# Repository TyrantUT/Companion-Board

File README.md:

# Companion-Board
4 Channel DC Relay for HLT / Boil Contactors, and HLT / Boil PWM

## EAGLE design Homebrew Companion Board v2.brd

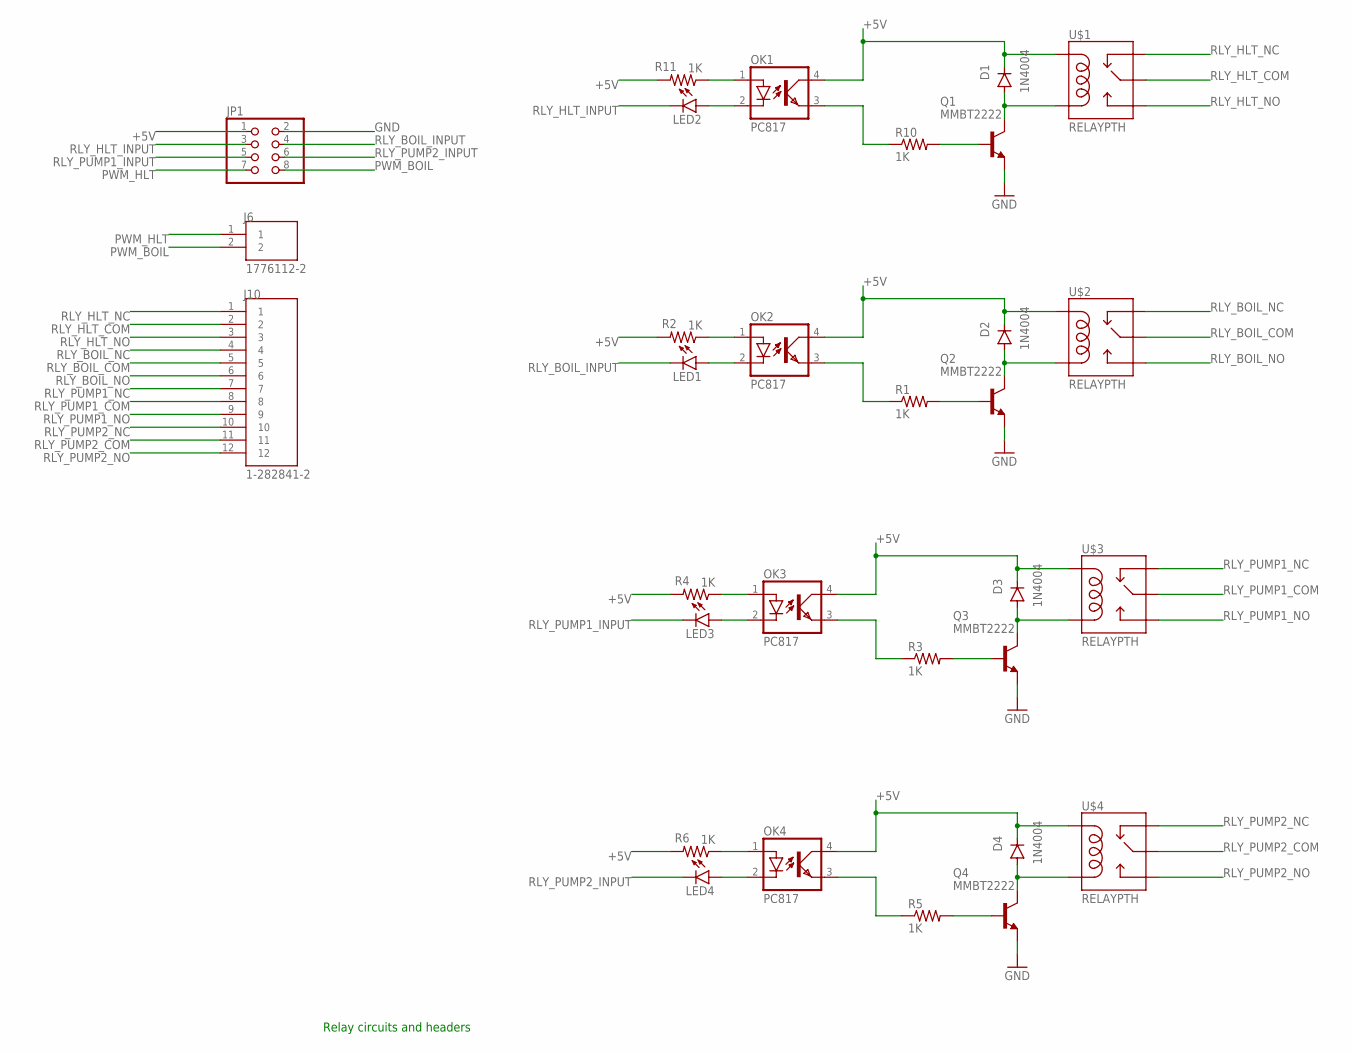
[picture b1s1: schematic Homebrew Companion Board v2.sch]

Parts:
D1, D2, D3, D4: 1N4004; DO41-10; MPN 1N4007-T
J6: 1776112-2; TE_1776112-2; MPN 1776112-2
J10: 1-282841-2; TE_1-282841-2; MPN 1-282841-2
JP1: PINHD-2X4; 2X04; MPN 826634-4
LED1, LED2, LED3, LED4: LEDCHIP-LED0805; CHIP-LED0805; MPN 5988110107F
OK1, OK2, OK3, OK4: PC817; DIL04; MPN HCPL-817-000E
Q1, Q2, Q3, Q4: MMBT2222; SOT23-BEC; MPN MMBT2222A-7-F
R1, R2, R3, R4, R5, R6, R10, R11: 1K; R0603; MPN AC0402FR-071KL
U$1, U$2, U$3, U$4: RELAYPTH; SRD-05VDC-SL-C

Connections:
+5V: D1.C, D2.C, D3.C, D4.C, JP1.1, OK1.4 (COL), OK2.4 (COL), OK3.4 (COL), OK4.4 (COL), R2.2, R4.2, R6.2, R11.2, U$1.COIL1, U$2.COIL1, U$3.COIL1, U$4.COIL1
GND: JP1.2, Q1.E, Q2.E, Q3.E, Q4.E
unnamed: D2.A, Q2.C, U$2.COIL0
unnamed: D1.A, Q1.C, U$1.COIL0
unnamed: LED2.A, OK1.2 (C)
unnamed: Q1.B, R10.2
unnamed: OK1.3 (EMIT), R10.1
unnamed: OK1.1 (A), R11.1
unnamed: LED1.A, OK2.2 (C)
unnamed: Q2.B, R1.2
unnamed: OK2.3 (EMIT), R1.1
unnamed: OK2.1 (A), R2.1
unnamed: D3.A, Q3.C, U$3.COIL0
unnamed: LED3.A, OK3.2 (C)
unnamed: Q3.B, R3.2
unnamed: OK3.3 (EMIT), R3.1
unnamed: OK3.1 (A), R4.1
unnamed: D4.A, Q4.C, U$4.COIL0
unnamed: LED4.A, OK4.2 (C)
unnamed: Q4.B, R5.2
unnamed: OK4.3 (EMIT), R5.1
unnamed: OK4.1 (A), R6.1
PWM_BOIL: J6.2, JP1.8
PWM_HLT: J6.1, JP1.7
RLY_BOIL_COM: J10.5, U$2.SWCOMMON
RLY_BOIL_INPUT: JP1.4, LED1.C
RLY_BOIL_NC: J10.4, U$2.SWCLOSED (SWCLOSE)
RLY_BOIL_NO: J10.6, U$2.SWOPEN
RLY_HLT_COM: J10.2, U$1.SWCOMMON
RLY_HLT_INPUT: JP1.3, LED2.C
RLY_HLT_NC: J10.1, U$1.SWCLOSED (SWCLOSE)
RLY_HLT_NO: J10.3, U$1.SWOPEN
RLY_PUMP1_COM: J10.8, U$3.SWCOMMON
RLY_PUMP1_INPUT: JP1.5, LED3.C
RLY_PUMP1_NC: J10.7, U$3.SWCLOSED (SWCLOSE)
RLY_PUMP1_NO: J10.9, U$3.SWOPEN
RLY_PUMP2_COM: J10.11, U$4.SWCOMMON
RLY_PUMP2_INPUT: JP1.6, LED4.C
RLY_PUMP2_NC: J10.10, U$4.SWCLOSED (SWCLOSE)
RLY_PUMP2_NO: J10.12, U$4.SWOPEN

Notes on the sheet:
Relay circuits and headers

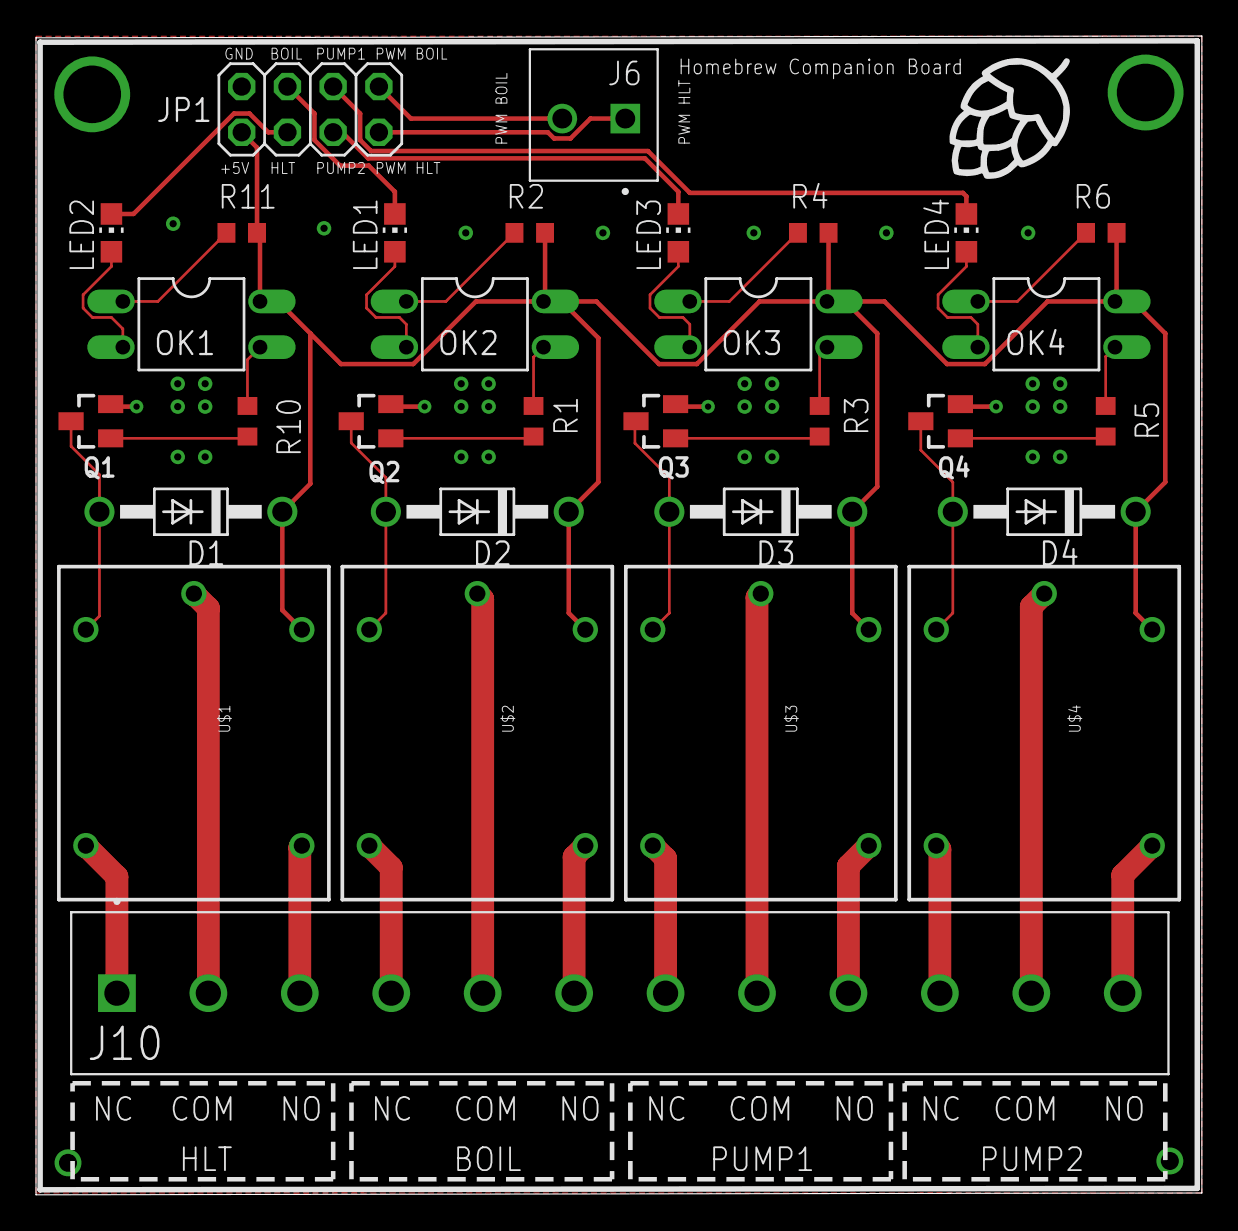
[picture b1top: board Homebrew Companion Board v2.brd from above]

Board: 2 copper layers, 64.8 x 64.4 mm, 31 parts (0 on the bottom side), 40 nets.
